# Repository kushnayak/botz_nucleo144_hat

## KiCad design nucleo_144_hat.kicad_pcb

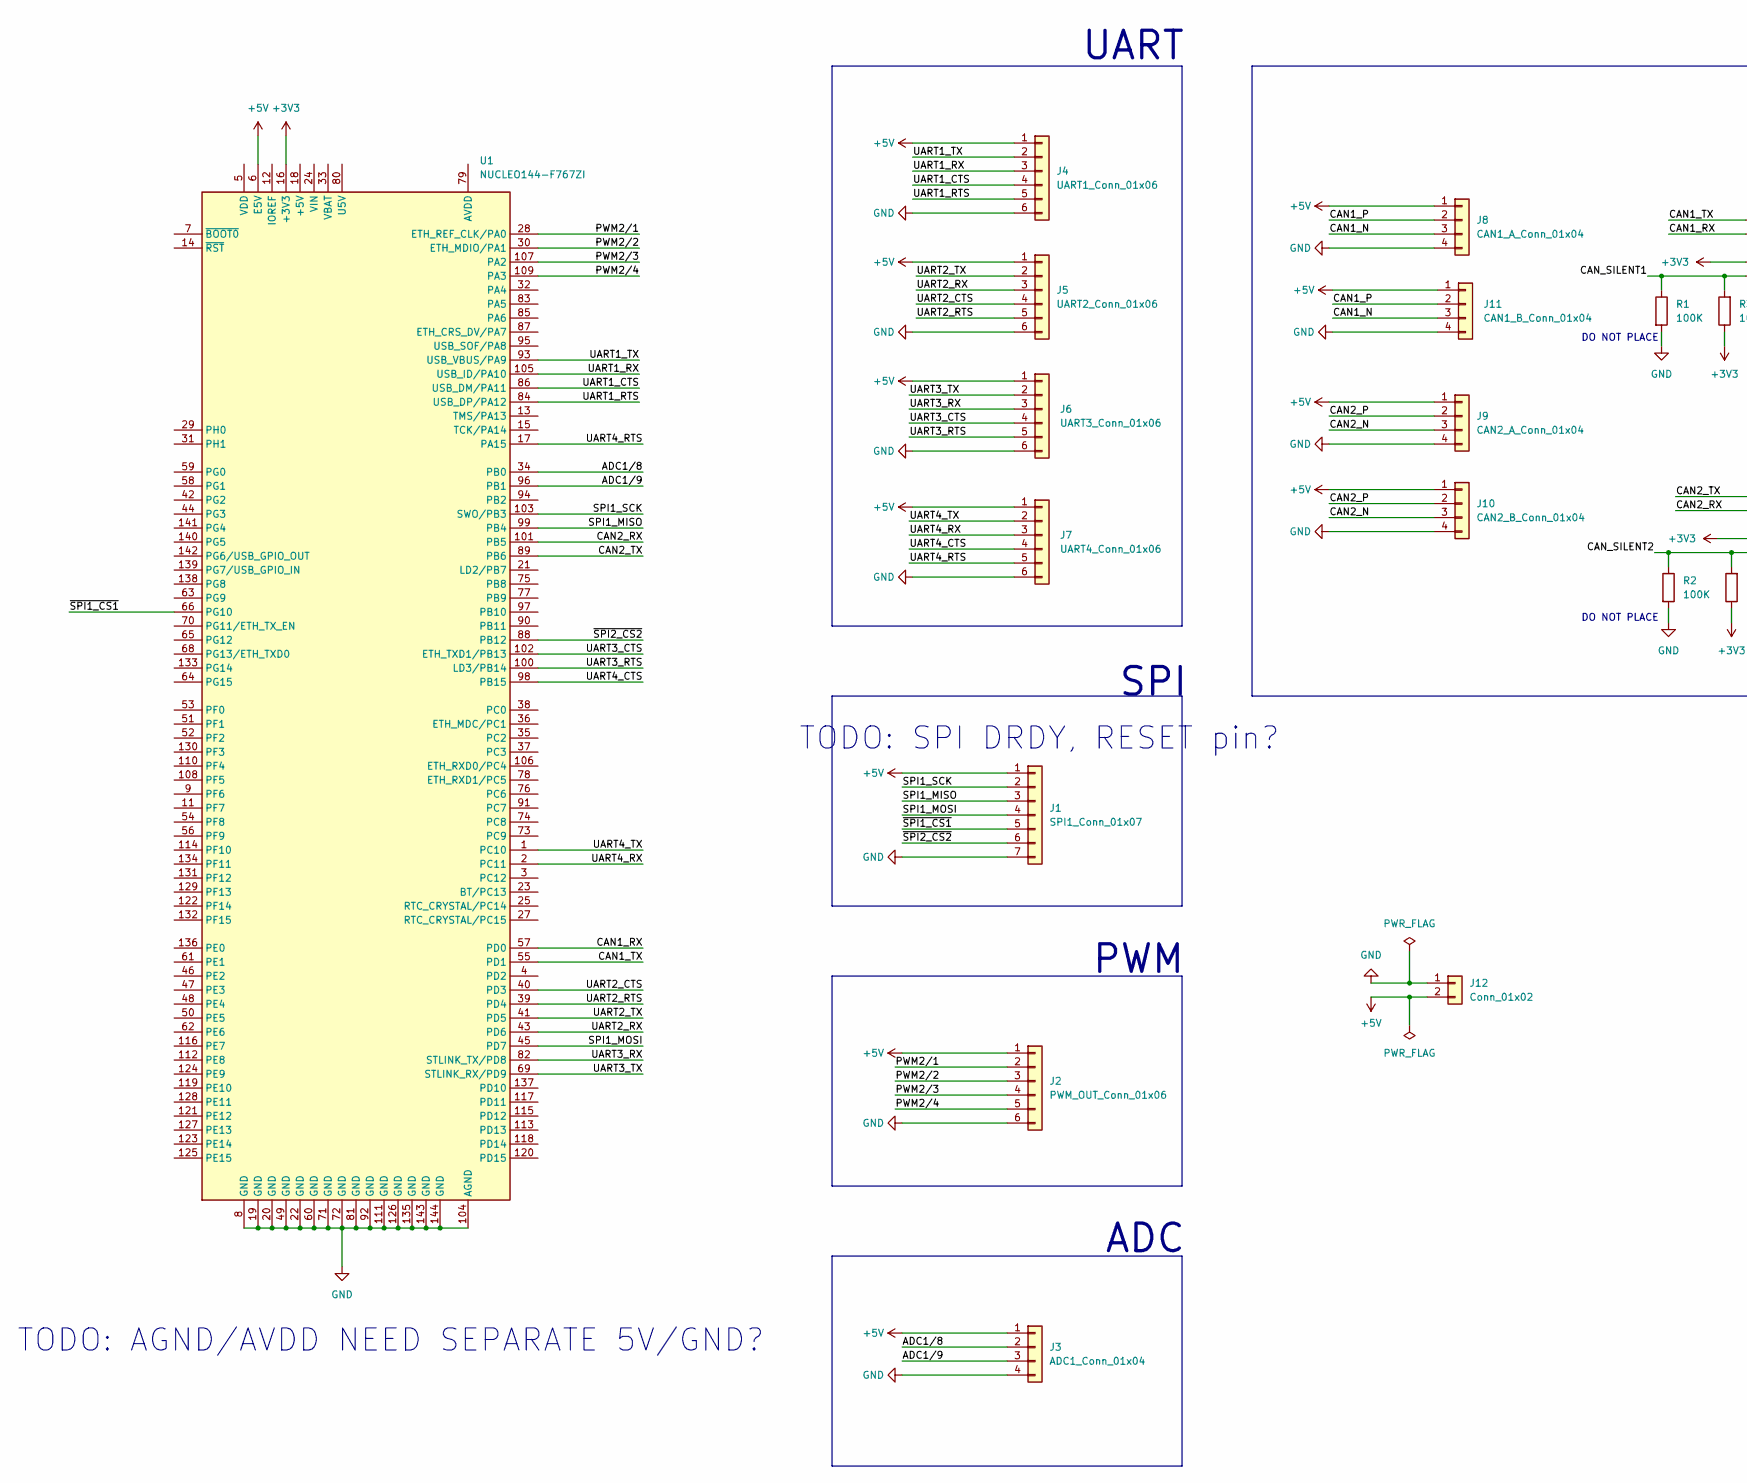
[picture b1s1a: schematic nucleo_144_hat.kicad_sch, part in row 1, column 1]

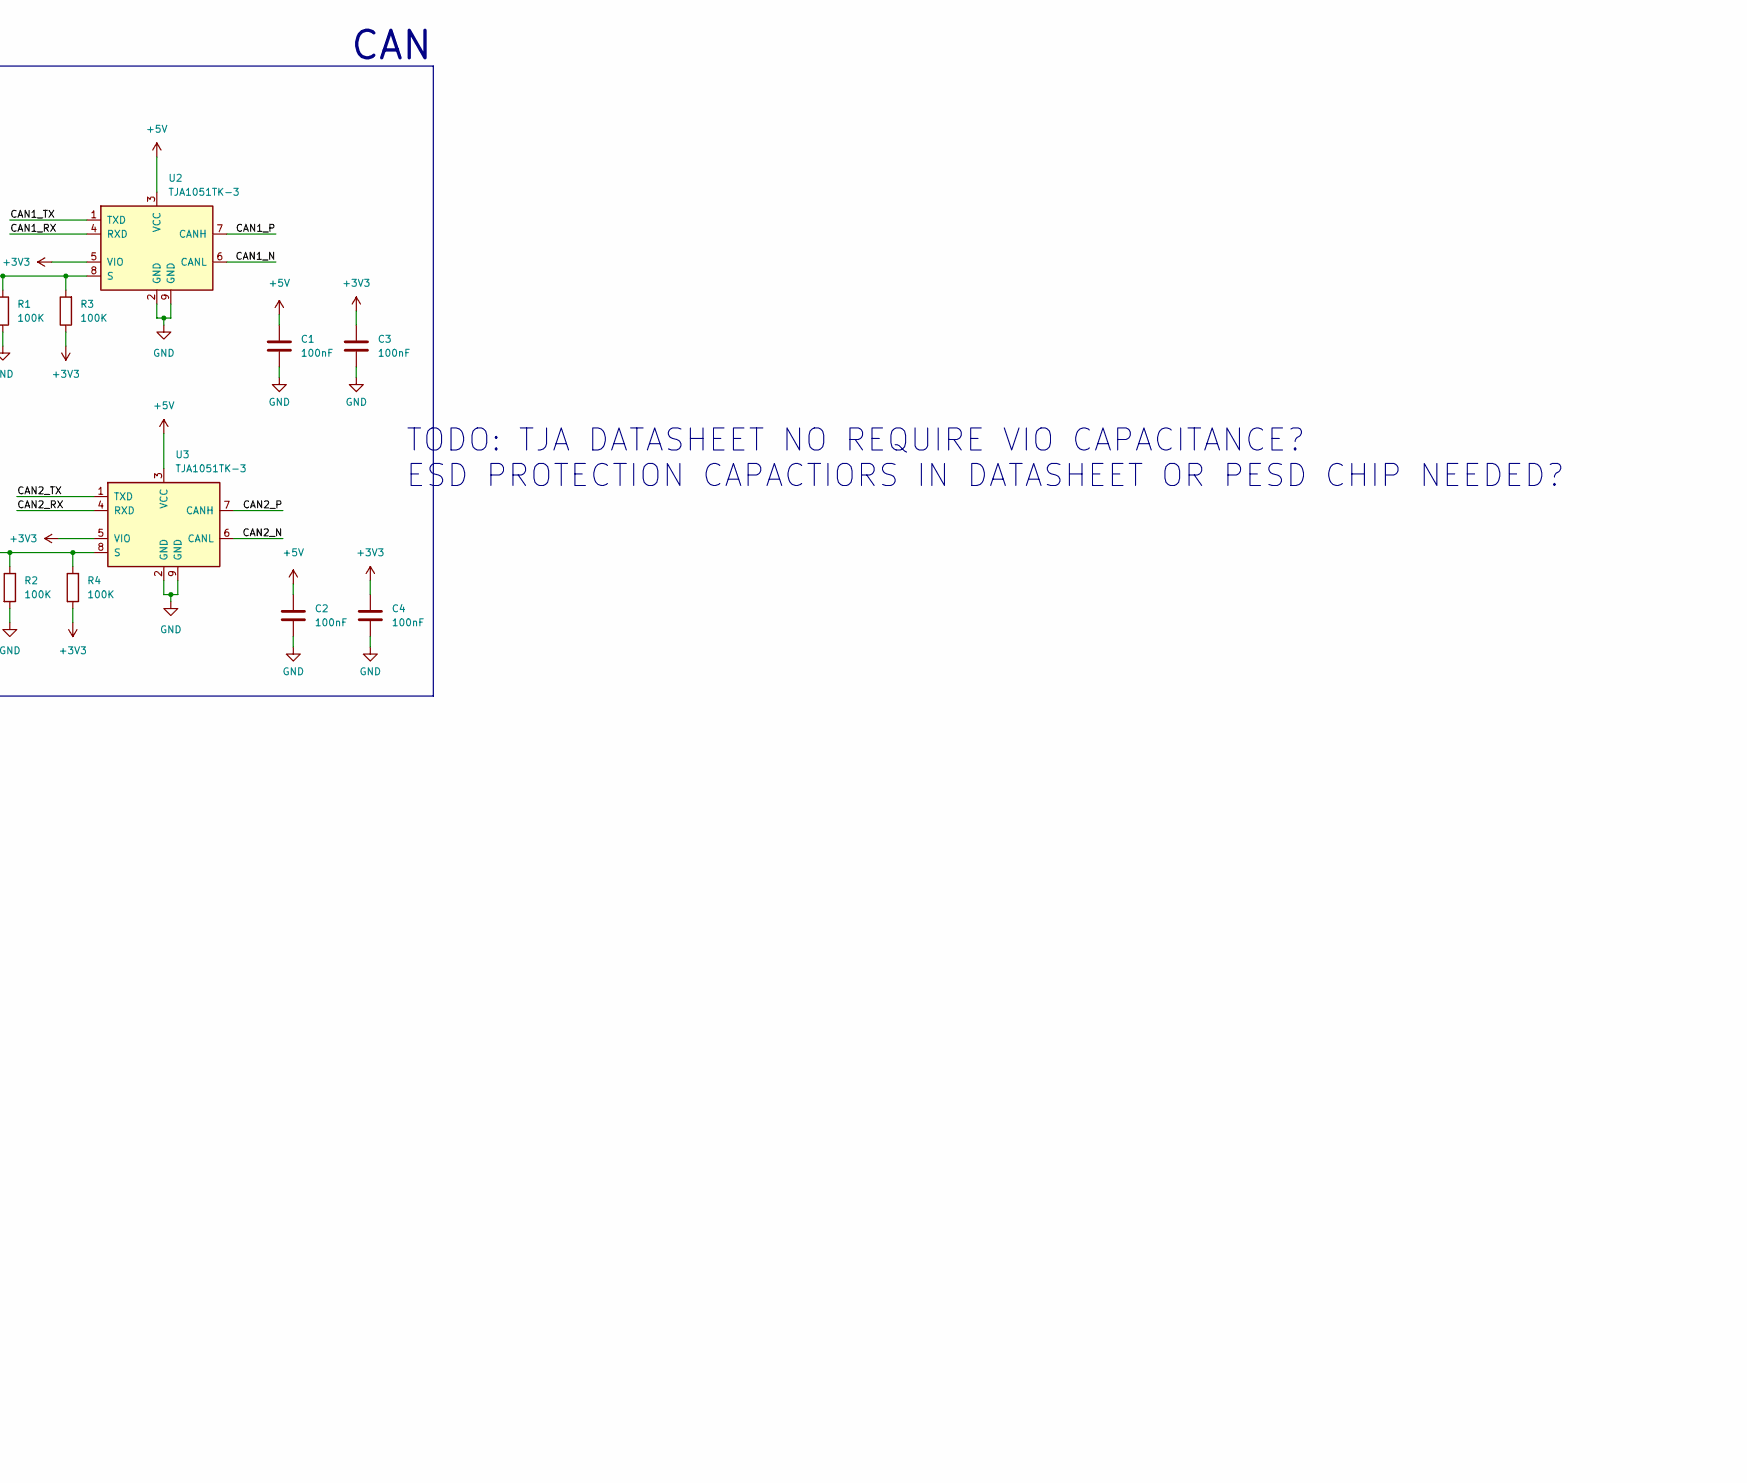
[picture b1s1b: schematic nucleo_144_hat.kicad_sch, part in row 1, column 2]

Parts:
C1, C2, C3, C4: 100nF; C_0603_1608Metric
J1: SPI1_Conn_01x07; JST_GH_SM07B-GHS-TB_1x07-1MP_P1.25mm_Horizontal
J2: PWM_OUT_Conn_01x06; JST_GH_SM06B-GHS-TB_1x06-1MP_P1.25mm_Horizontal
J3: ADC1_Conn_01x04; JST_GH_SM04B-GHS-TB_1x04-1MP_P1.25mm_Horizontal
J4: UART1_Conn_01x06; JST_GH_SM06B-GHS-TB_1x06-1MP_P1.25mm_Horizontal
J5: UART2_Conn_01x06; JST_GH_SM06B-GHS-TB_1x06-1MP_P1.25mm_Horizontal
J6: UART3_Conn_01x06; JST_GH_SM06B-GHS-TB_1x06-1MP_P1.25mm_Horizontal
J7: UART4_Conn_01x06; JST_GH_SM06B-GHS-TB_1x06-1MP_P1.25mm_Horizontal
J8: CAN1_A_Conn_01x04; JST_GH_SM04B-GHS-TB_1x04-1MP_P1.25mm_Horizontal
J9: CAN2_A_Conn_01x04; JST_GH_SM04B-GHS-TB_1x04-1MP_P1.25mm_Horizontal
J10: CAN2_B_Conn_01x04; JST_GH_SM04B-GHS-TB_1x04-1MP_P1.25mm_Horizontal
J11: CAN1_B_Conn_01x04; JST_GH_SM04B-GHS-TB_1x04-1MP_P1.25mm_Horizontal
J12: Conn_01x02; Molex_CLIK-Mate_502386-0270_1x02-1MP_P1.25mm_Horizontal
R1, R2, R3, R4: 100K; R_0603_1608Metric
U1: NUCLEO144-F767ZI; nucleo144_hat
U2, U3: TJA1051TK-3; DFN-8-1EP_3x3mm_P0.65mm_EP1.55x2.4mm

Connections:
+3V3: C3.1, C4.1, R3.1, R4.1, U1.16 (+3V3), U2.5 (VIO), U3.5 (VIO)
+5V: C1.1, C2.1, J1.1, J2.1, J3.1, J4.1, J5.1, J6.1, J7.1, J8.1, J9.1, J10.1, J11.1, J12.2, U1.6 (E5V), U2.3 (VCC), U3.3 (VCC)
/ADC1/8: J3.2, U1.34 (PB0)
/ADC1/9: J3.3, U1.96 (PB1)
/CAN1_N: J8.3, J11.3, U2.6 (CANL)
/CAN1_P: J8.2, J11.2, U2.7 (CANH)
/CAN1_RX: U1.57 (PD0), U2.4 (RXD)
/CAN1_TX: U1.55 (PD1), U2.1 (TXD)
/CAN2_N: J9.3, J10.3, U3.6 (CANL)
/CAN2_P: J9.2, J10.2, U3.7 (CANH)
/CAN2_RX: U1.101 (PB5), U3.4 (RXD)
/CAN2_TX: U1.89 (PB6), U3.1 (TXD)
/CAN_SILENT1: R1.1, R3.2, U2.8 (S)
/CAN_SILENT2: R2.1, R4.2, U3.8 (S)
/PWM2/1: J2.2, U1.28 (ETH_REF_CLK/PA0)
/PWM2/2: J2.3, U1.30 (ETH_MDIO/PA1)
/PWM2/3: J2.4, U1.107 (PA2)
/PWM2/4: J2.5, U1.109 (PA3)
/SPI1_MISO: J1.3, U1.99 (PB4)
/SPI1_MOSI: J1.4, U1.45 (PD7)
/SPI1_SCK: J1.2, U1.103 (SWO/PB3)
/UART1_CTS: J4.4, U1.86 (USB_DM/PA11)
/UART1_RTS: J4.5, U1.84 (USB_DP/PA12)
/UART1_RX: J4.3, U1.105 (USB_ID/PA10)
/UART1_TX: J4.2, U1.93 (USB_VBUS/PA9)
/UART2_CTS: J5.4, U1.40 (PD3)
/UART2_RTS: J5.5, U1.39 (PD4)
/UART2_RX: J5.3, U1.43 (PD6)
/UART2_TX: J5.2, U1.41 (PD5)
/UART3_CTS: J6.4, U1.102 (ETH_TXD1/PB13)
/UART3_RTS: J6.5, U1.100 (LD3/PB14)
/UART3_RX: J6.3, U1.82 (STLINK_TX/PD8)
/UART3_TX: J6.2, U1.69 (STLINK_RX/PD9)
/UART4_CTS: J7.4, U1.98 (PB15)
/UART4_RTS: J7.5, U1.17 (PA15)
/UART4_RX: J7.3, U1.2 (PC11)
/UART4_TX: J7.2, U1.1 (PC10)
/~SPI1_CS1: J1.5, U1.66 (PG10)
/~SPI2_CS2: J1.6, U1.88 (PB12)
GND: C1.2, C2.2, C3.2, C4.2, J1.7, J2.6, J3.4, J4.6, J5.6, J6.6, J7.6, J8.4, J9.4, J10.4, J11.4, J12.1, R1.2, R2.2, U1.8 (GND), U1.19 (GND), U1.20 (GND), U1.22 (GND), U1.49 (GND), U1.60 (GND), U1.71 (GND), U1.72 (GND), U1.81 (GND), U1.92 (GND), U1.104 (AGND), U1.111 (GND), U1.126 (GND), U1.135 (GND), U1.143 (GND), U1.144 (GND), U2.2 (GND), U2.9 (GND), U3.2 (GND), U3.9 (GND)

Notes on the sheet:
TODO: AGND/AVDD NEED SEPARATE 5V/GND?
DO NOT PLACE
PWM
TODO: TJA DATASHEET NO REQUIRE VIO CAPACITANCE? ESD PROTECTION CAPACTIORS IN DATASHEET OR PESD CHIP NEEDED?
ADC
SPI
TODO: SPI DRDY, RESET pin?
CAN
UART

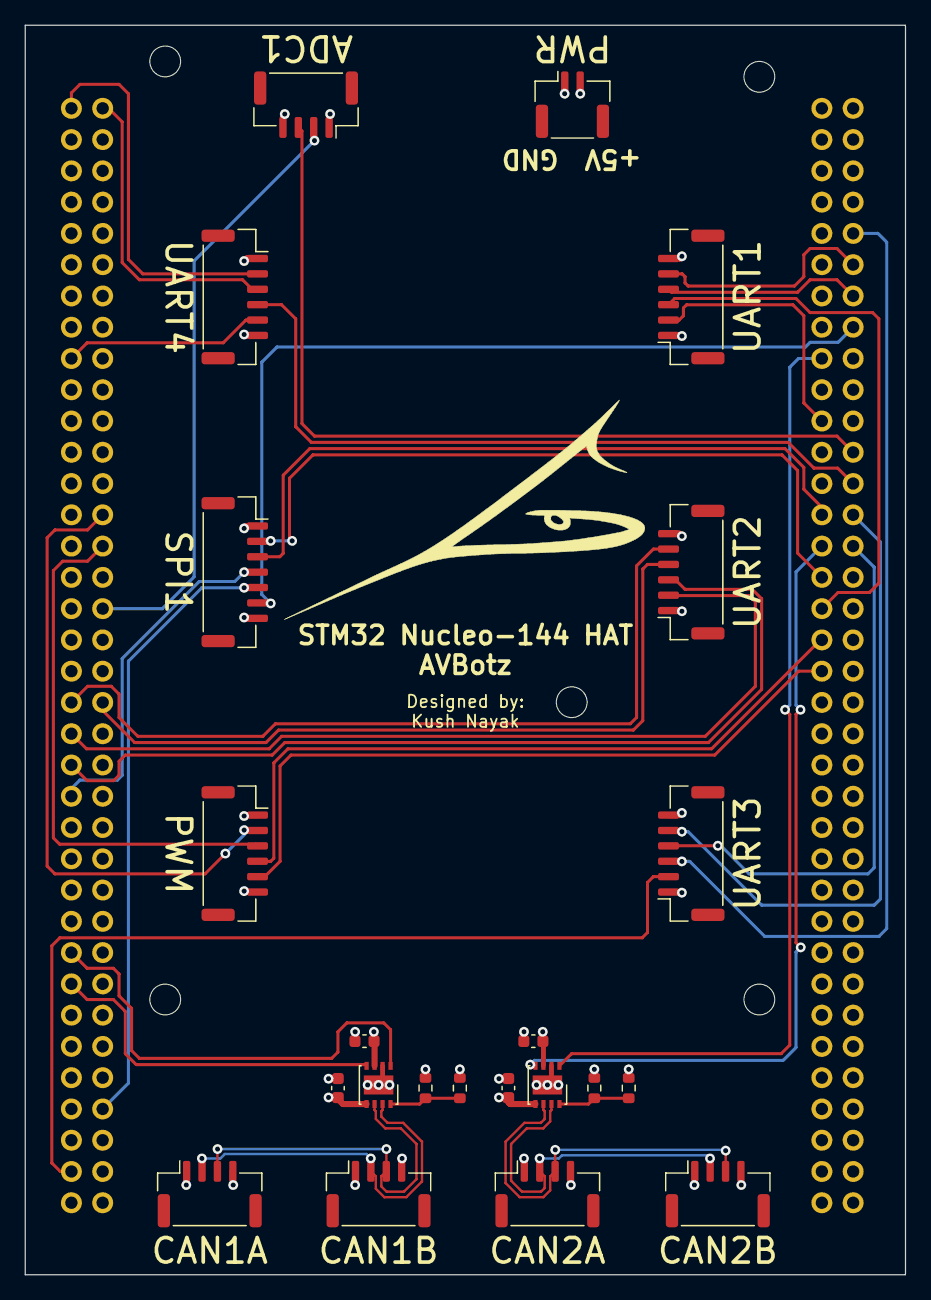
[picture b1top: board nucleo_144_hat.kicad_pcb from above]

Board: 4 copper layers, 71.5 x 101.5 mm, 23 parts (0 on the bottom side), 40 nets.

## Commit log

2022-09-11 update molex conn ref to use local 3d model
2022-09-11 clean up tracing
